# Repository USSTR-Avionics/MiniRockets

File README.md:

# University of Saskatchewan Space Design Team: Avionics

---

# Rocket Autonomy System

Welcome to the Rocket Autonomy System project, developed by the University of Saskatchewan Space Design Team (USST). This software project aims to create a complete autonomous system for rockets.

## Project Overview

The primary goal of this project is to design and implement an autonomous system for rockets that exhibits three main capabilities:

1. **Command**: The system is designed to send/receive commands to/from a ground station in real-time. It should also be capable of executing received commands on the rocket promptly.

2. **Control**: The system will quasi-autonomously control the rocket, ensuring stable flight state detection. This includes phases such as powered flight, ballistic descent, and controlled parachute deployment.

3. **Data Acquisition**: The system must collect data from various sensors within the rocket. Collected data should be transmitted to the ground station in real-time, enabling real-time monitoring and analysis of the rocket's performance during flight.

## Key Objectives

The Rocket Autonomy System project encompasses the following key objectives:

- **Parachute Deployment**: The system will implement logic for accurate deployment of a parachute at the rocket's apogee, ensuring a safe descent and recovery.

- **Data Collection and Storage**: The system will gather sensor data from onboard components, including accelerometers, barometric pressure sensors, thermocouples, and other relevant sensors. Collected data will be stored for analysis.

- **Ground Station Communication**: The system will establish a robust communication link between the rocket and a ground station. This link enables real-time exchange of commands and telemetry data, enhancing situational awareness and control.

## Mini Rocket Flight Computer Prototype

The project began with the development of the Mini Rocket Flight Computer prototype. This early prototype was crafted using commercial off-the-shelf breakout boards assembled onto PCBs. The prototype aimed to demonstrate the system's capabilities, including:

- Parachute deployment
- Data logging from sensors

### PCB Design

The PCB design was completed using Eagle, a commonly used PCB design tool.

### Version 1 (Engineering Model)

The initial version, known as the Engineering Model, served as a proof of concept. It successfully demonstrated the planned functionalities, laying the foundation for the Rocket Autonomy System project.

### Version 2 (Flight Model)

The second version, referred to as the Flight Model, brought significant enhancements to the Mini Rocket Flight Computer:

- Added additional breakout boards, including a thermocouple and a 32kByte FRAM for expanded data storage capacity.
- Improved power trace reliability for enhanced performance and reliability.
- Incorporated design modifications, including a gap in the middle of the system to meet aerostructure requirements.

#### Sensors

A variety of commercial off-the-shelf breakout sensors were utilized to develop and test the design rapidly. The design involved testing the following breakout boards:

- Teensy 4.1 Development Board (PJRC)
- KX134 Breakout (SparkFun)
- BNO055 IMU Breakout (Adafruit)
- BMI088 IMU Breakout (Mouser)
- MS5611 Breakout (Smart Prototyping)
- BMP280 Barometer (Adafruit)
- 32kByte FRAM Breakout (Adafruit)
- MAX31855 Thermocouple Breakout (Adafruit)
- RFM95W LoRa Radio Transceiver Breakout (Adafruit)
- DMC809 Servo Motors (RobotShop) (Not used in the final design)

#### Software

The software was written in C++ using PlatformIO in Visual Studio Code.

#### Lessons Learned

Through the development process, the team gained valuable insights:

- Teensy 4.1 is highly efficient for rapid code development.
- KX134 accelerometer is exceptionally capable, measuring up to 64g's of acceleration.
- BNO055's sensor fusion algorithms aren't suitable for rockets due to their dependency on downward acceleration being 9.81m/s^2.
- BMI088 worked well, but its non-standard header pins posed challenges for breadboard testing.
- MS5611 and BMP280 performed effectively.
- 32kBytes of FRAM storage proved barely sufficient for minimal rocket data, even with data compression.
- MAX31855 reliably operated, even with thermocouples from different suppliers.
- RFM95W LoRa Radios functioned well, though integrating libraries into PlatformIO presented some difficulties.
- Servo motors are unsuitable for parachute deployment systems.
- Modularization was vital, with the main program containing only essential components.

Thank you for your interest in the Rocket Autonomy System project. Together, we can push the boundaries of rocket technology and contribute to the advancement of autonomous rocket systems.

<p align="center">  </img> </p>

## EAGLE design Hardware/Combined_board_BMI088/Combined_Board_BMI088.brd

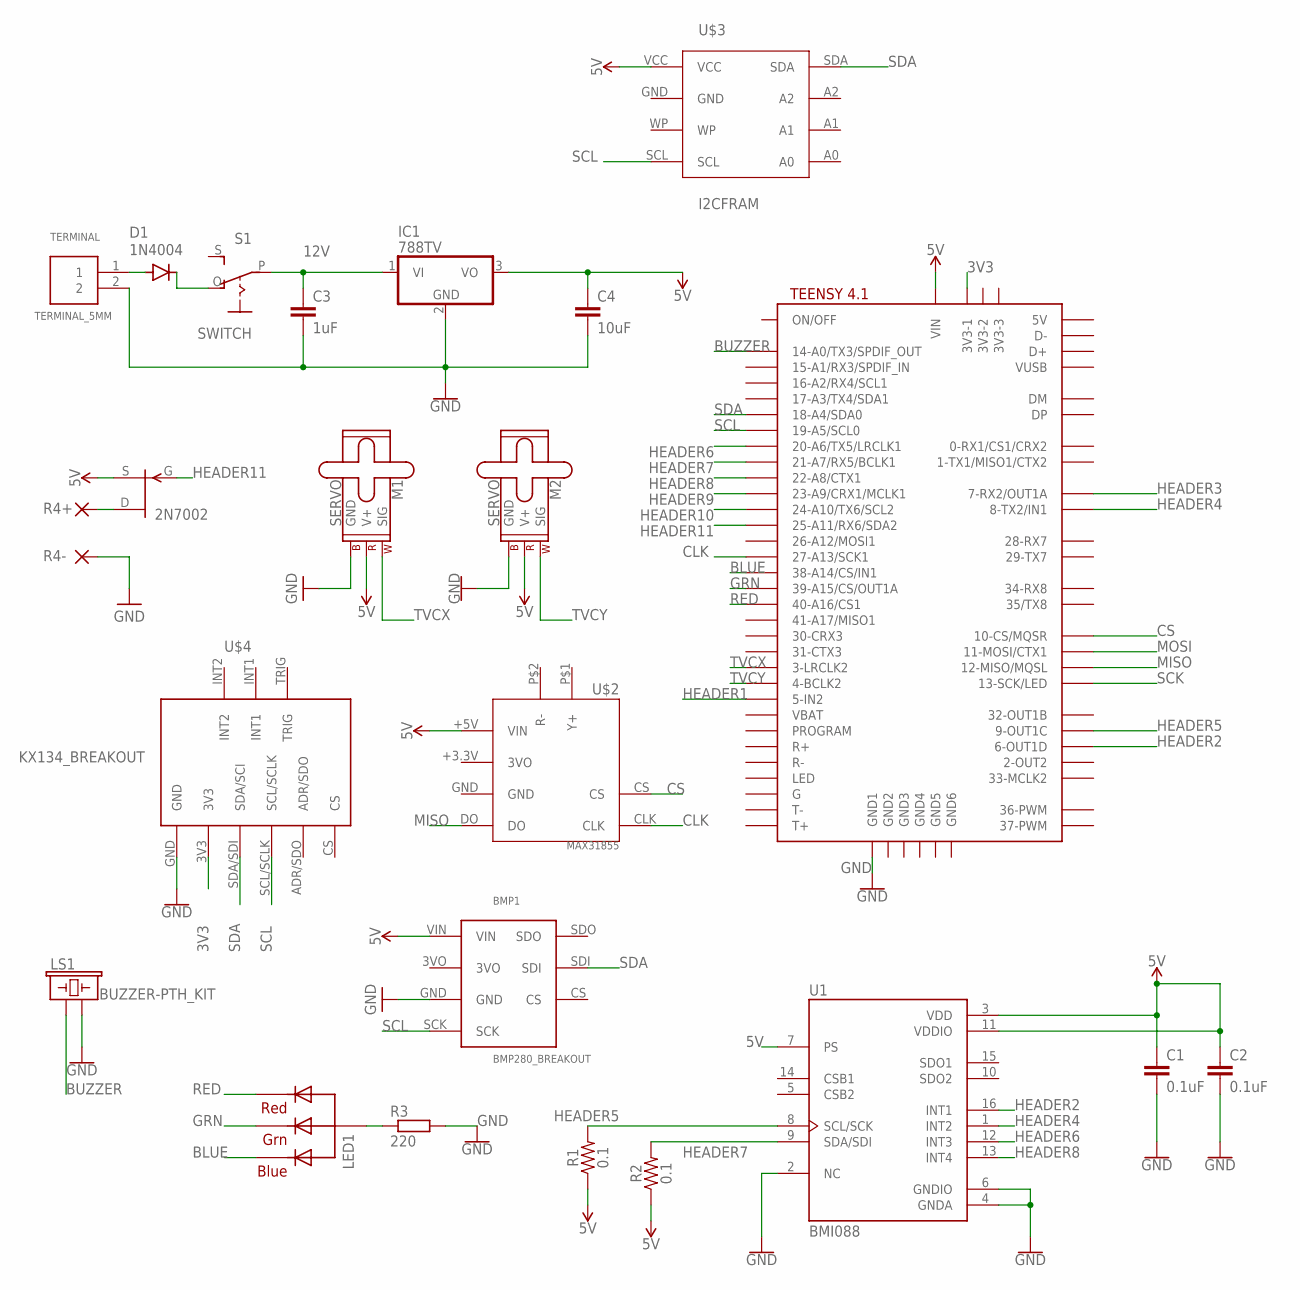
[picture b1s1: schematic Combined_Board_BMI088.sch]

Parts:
2N7002: 2N3819; TO92
BMP1: BMP280_BREAKOUT
C1, C2: 0.1uF; 0402
C3: 1uF; CAP-PTH-2.54
C4: 10uF; CAP-PTH-2.54
D1: 1N4004; DO41-10
IC1: 788TV; TO220V
LED1: RGBLED_CA-5MM; LED5MMRGB
LS1: BUZZER-PTH_KIT; BUZZER-12MM-KIT
M1, M2: SERVO; 1X03
R1, R2: 0.1; 0603
R3: 220; 0204/7
R4+, R4-: 1,6/0,8
S1: SWITCH; EG1218
TERMINAL: TERMINAL_5MM
U1: BMI088; PQFN50P450X300X100-16N
U$1: TEENSY41
U$2: MAX31855; MAX31855-BREAKOUT
U$3: I2CFRAM
U$4: KX134_BREAKOUT

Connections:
3V3: U$1.3V3-1, U$4.3V3
5V: 2N7002.3 (S), BMP1.VIN, C1.1, C2.1, C4.1, IC1.3 (VO), M1.2 (V+), M2.2 (V+), R1.1, R2.1, U1.3 (VDD), U1.7 (PS), U1.11 (VDDIO), U$1.VIN, U$2.+5V (VIN), U$3.VCC
12V: C3.1, IC1.1 (VI), S1.P
BLUE: LED1.4 (BLUE), U$1.38-A14/CS/IN1
BUZZER: LS1.+ (1), U$1.14-A0/TX3/SPDIF_OUT
CLK: U$1.27-A13/SCK1, U$2.CLK
CS: U$1.10-CS\MQSR (10-CS/MQSR), U$2.CS
GND: BMP1.GND, C1.2, C2.2, C3.2, C4.2, IC1.2 (GND), LS1.- (2), M1.3 (GND), M2.3 (GND), R3.2, R4-.1, TERMINAL.2, U1.2 (NC), U1.4 (GNDA), U1.6 (GNDIO), U$1.GND1, U$4.GND
GRN: LED1.3 (GREEN), U$1.39-A15/CS/OUT1A
HEADER1: U$1.5-IN2
HEADER2: U1.16 (INT1), U$1.6-OUT1D
HEADER3: U$1.7-RX2/OUT1A
HEADER4: U1.1 (INT2), U$1.8-TX2/IN2 (8-TX2/IN1)
HEADER5: R1.2, U1.8 (SCL/SCK), U$1.9-OUT1C
HEADER6: U1.12 (INT3), U$1.20-A6/TX5/LRCLK1
HEADER7: R2.2, U1.9 (SDA/SDI), U$1.21-A7/RX5/BCLK1
HEADER8: U1.13 (INT4), U$1.22-A8/CTX1
HEADER9: U$1.23-A9/CRX1/MCLK1
HEADER10: U$1.24-A10/TX6/SCL2
HEADER11: 2N7002.2 (G), U$1.25-A11/RX6/SDA2
MISO: U$1.12-MISO/MQSL, U$2.DO
MOSI: U$1.11-MOSI/CTX1
unnamed: LED1.2 (VCC), R3.1
unnamed: D1.A, TERMINAL.1
unnamed: 2N7002.1 (D), R4+.1
unnamed: D1.C, S1.O
RED: LED1.1 (RED), U$1.40-A16/CS1
SCK: U$1.13-SCK/LED
SCL: BMP1.SCK, U$1.19-A5/SCL0, U$3.SCL, U$4.SCL/SCLK
SDA: BMP1.SDI, U$1.18-A4/SDA0, U$3.SDA, U$4.SDA/SDI (SDA/SCI)
TVCX: M1.1 (SIG), U$1.3-LRCLK2
TVCY: M2.1 (SIG), U$1.4-BCLK2

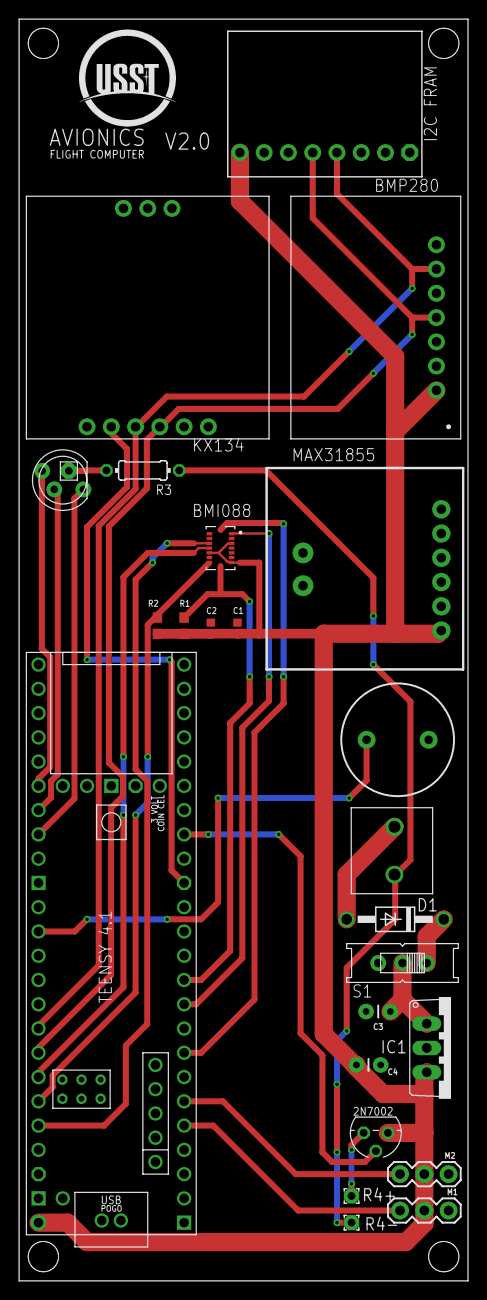
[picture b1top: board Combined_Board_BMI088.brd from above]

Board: 2 copper layers, 47.0 x 132.1 mm, 24 parts (0 on the bottom side), 26 nets.

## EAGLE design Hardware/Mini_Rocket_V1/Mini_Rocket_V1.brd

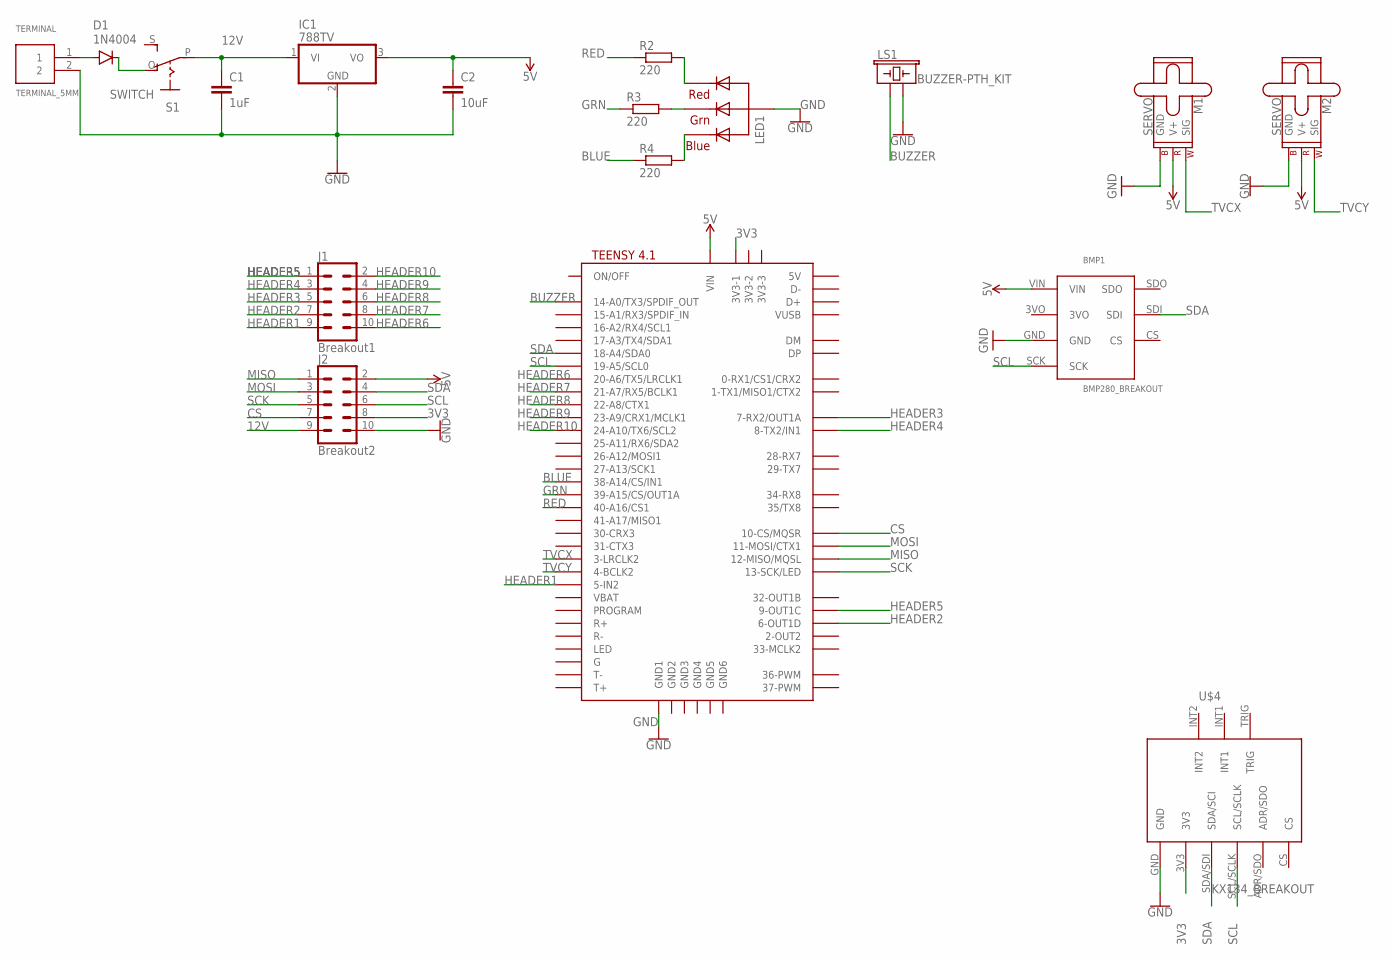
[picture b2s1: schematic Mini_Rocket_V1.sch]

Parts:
BMP1: BMP280_BREAKOUT
C1: 1uF; CAP-PTH-2.54
C2: 10uF; CAP-PTH-2.54
D1: 1N4004; DO41-10
IC1: 788TV; TO220V
J1: Breakout1; 2X5_NOSILK
J2: Breakout2; 2X5_NOSILK
LED1: RGBLED_CA-5MM; LED5MMRGB
LS1: BUZZER-PTH_KIT; BUZZER-12MM-KIT
M1, M2: SERVO; 1X03
R2, R3, R4: 220; 0204/7
S1: SWITCH; EG1218
TERMINAL: TERMINAL_5MM
U$1: TEENSY41
U$4: KX134_BREAKOUT

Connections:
3V3: J2.8, U$1.3V3-1, U$4.3V3
5V: BMP1.VIN, C2.1, IC1.3 (VO), J2.2, M1.2 (V+), M2.2 (V+), U$1.VIN
12V: C1.1, IC1.1 (VI), J2.9, S1.P
BLUE: R4.1, U$1.38-A14/CS/IN1
BUZZER: LS1.+ (1), U$1.14-A0/TX3/SPDIF_OUT
CS: J2.7, U$1.10-CS\MQSR (10-CS/MQSR)
GND: BMP1.GND, C1.2, C2.2, IC1.2 (GND), J2.10, LED1.2 (VCC), LS1.- (2), M1.3 (GND), M2.3 (GND), TERMINAL.2, U$1.GND1, U$4.GND
GRN: R3.1, U$1.39-A15/CS/OUT1A
HEADER1: J1.9, U$1.5-IN2
HEADER2: J1.7, U$1.6-OUT1D
HEADER3: J1.5, U$1.7-RX2/OUT1A
HEADER4: J1.3, U$1.8-TX2/IN2 (8-TX2/IN1)
HEADER5: J1.1, U$1.9-OUT1C
HEADER6: J1.10, U$1.20-A6/TX5/LRCLK1
HEADER7: J1.8, U$1.21-A7/RX5/BCLK1
HEADER8: J1.6, U$1.22-A8/CTX1
HEADER9: J1.4, U$1.23-A9/CRX1/MCLK1
HEADER10: J1.2, U$1.24-A10/TX6/SCL2
MISO: J2.1, U$1.12-MISO/MQSL
MOSI: J2.3, U$1.11-MOSI/CTX1
unnamed: LED1.1 (RED), R2.2
unnamed: LED1.3 (GREEN), R3.2
unnamed: LED1.4 (BLUE), R4.2
unnamed: D1.A, TERMINAL.1
unnamed: D1.C, S1.O
RED: R2.1, U$1.40-A16/CS1
SCK: J2.5, U$1.13-SCK/LED
SCL: BMP1.SCK, J2.6, U$1.19-A5/SCL0, U$4.SCL/SCLK
SDA: BMP1.SDI, J2.4, U$1.18-A4/SDA0, U$4.SDA/SDI (SDA/SCI)
TVCX: M1.1 (SIG), U$1.3-LRCLK2
TVCY: M2.1 (SIG), U$1.4-BCLK2

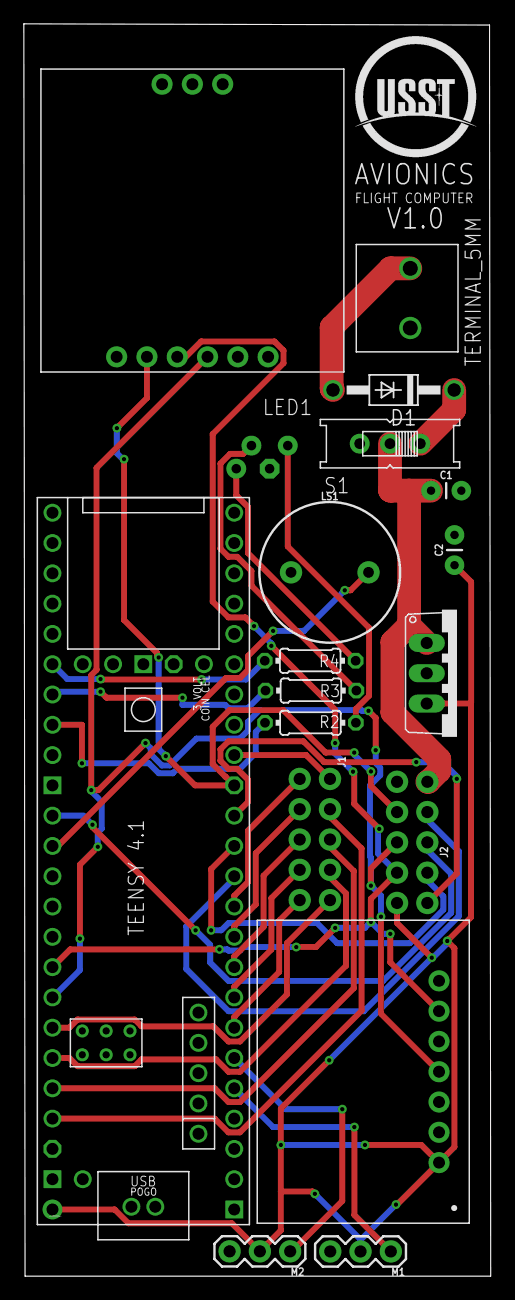
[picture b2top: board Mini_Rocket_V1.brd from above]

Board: 2 copper layers, 39.1 x 105.0 mm, 18 parts (1 on the bottom side), 31 nets.

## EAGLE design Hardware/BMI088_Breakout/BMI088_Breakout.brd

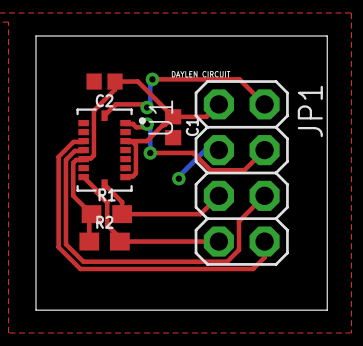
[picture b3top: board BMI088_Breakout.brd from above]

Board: 2 copper layers, 16.2 x 15.2 mm, 6 parts (0 on the bottom side), 8 nets.

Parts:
C1, C2: 0.1uF; 0402
JP1: 2X04
R1, R2: 0.1; 0603
U1: BMI088; PQFN50P450X300X100-16N

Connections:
GND: C1.2, C2.2, JP1.3, U1.2, U1.4, U1.6
HEADER2: JP1.2, U1.16
HEADER4: JP1.4, U1.1
HEADER5: JP1.5, R1.2, U1.8
HEADER6: JP1.6, U1.12
HEADER7: JP1.7, R2.2, U1.9
HEADER8: JP1.8, U1.13
VIN: C1.1, C2.1, JP1.1, R1.1, R2.1, U1.3, U1.7, U1.11

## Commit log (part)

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2022-10-30 completed write()
2022-10-30 removed rounding
2022-10-30 Finished IO functions(write(), read())
2022-10-30 Finished prototyping IO functions(write(), read()), 2's complement might be a concern
2022-10-30 added rounding
2022-10-30 increased memory limit 32k -> 32.768k
2022-10-30 added some comments
2022-10-30 updated .gitignore
2022-10-30 working on float representation in memory
2022-10-31 resolved merge conflicts
2022-10-31 mostly in sync with .ino code except for kalman filters, added preflight software checklist
2022-10-31 deleted inner .gitignore
2022-10-31 updated git cache on local
2022-10-31 started work on interface for fram writers
2022-11-01 patched m_Addr changes
2022-11-02 converting state stuct to enum
2022-11-02 fixed const char*
2022-11-02 deleted struct'
2022-11-02 FLODEF changed to not move into powered flight on rest
2022-11-05 read and write calculation tested and fixed
2022-11-06 0.4.0 - refactored code; tbd impl bmi088
2022-11-06 cleaned up meetTheTeam
2022-11-06 fixed merge conflicts
2022-11-06 added basic api abstraction for bmi088
2022-11-07 added i2c scanner, bmp280 returns no data
2022-11-07 bmp280 uses relative height
2022-11-07 sd does not work because builtin_sd macro not in lib
2022-11-08 added support for external LED
2022-11-08 implemented some util and settings, working on the handshake
2022-11-08 constructor fix
2022-11-09 need to perform hand shake
2022-11-11 0.5.0 - changed delays back to millis
2022-11-11 Added comments to main.cpp
2022-11-11 need testing
2022-11-11 removed unnecessary recursive call
2022-11-11 removed actions
2022-11-12 RX.cpp
2022-11-12 Avionics RX
2022-11-12 push
2022-11-13 added radiohead library
2022-11-19 added eagle files
2022-11-19 sd card module works sometimes
2022-11-19 fails init
2022-11-20 0.6.0 - updated SD lib
2022-11-26 added thermocouple library
2022-12-01 0.7.0 - added bmp280 relative altitude; added param defs in headers
2022-12-02 return a boxed struct; int/float -> string
2022-12-02 0.8.0 - logging to SD card now works
2022-12-02 0.9.0 - refactored and cleaned up code
2022-12-02 0.8.1 - fixed const char * declaration in header
2022-12-02 0.8.3 - fixed csv formatting
2022-12-03 0.8.4 - discriminating event and data log(s)
2022-12-03 sd works again
2022-12-24 Changed how serial data was printed out in flight (only have comma delimited values in the serial output if not in debug)
2022-12-24 Fixed ground idle to powered flight flawed transition state
2022-12-24 Fixed flawed transition from powered to unpowered flight. When acceleration < Liftoff_threshold it should transition to next state, also flawed implementation of millis() time check is fixed
2022-12-25 Updated apogee check function to properly detect apogee
2022-12-25 Updated deployment and land safe code
2022-12-26 modified led pins and added buzzer module
2022-12-28 Cleaned up code, added a test mode which currently allows the program to enter any state for testing purposes, made .h file for user variables that can be edited depending on what the user wants to t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
2022-12-28 added some more updates to testmode and updates to flight profile in test vs real flight
2022-12-31 updated state machine with MS5611 sensor rather than BMP280 since we are out of BMP280's
2023-01-01 Code clean up and change of vars for presentation
2023-01-14 sync
2023-01-15 general cleanup, cleaned ambiguous operator precedences
2023-01-15 removed random datafile
2023-01-15 fixed ODR violations; do not declare globals in header files!
2023-01-16 break i2c scanner into a debug header
2023-01-16 added ifndef guards
2023-01-16 debug mode is now macro dependent
2023-01-16 0.9.0 - renames and re-wraps
2023-01-16 0.9.1 - added compiler warnings to emit compile mode
2023-01-16 added additional checks to prevent accidental production builds
2023-01-16 consolidated README.md
2023-01-17 0.9.2 - added compiler flags to platform.ini file
2023-01-17 added comments for build flags
2023-01-18 changed doubles to floats; added RFC template
2023-01-21 testing out a workflow
2023-01-21 testing a build fail
2023-01-21 update .ini to include toolchain version
2023-01-21 0.8.5 - restructred folder
2023-01-21 added Links folder
2023-01-21 renamed folders
2023-01-21 Added name to meetTheTeam
2023-01-21 radio setup
2023-01-22 trying to unfuck dev
2023-01-22 trying a force push
2023-01-22 remove
2023-01-22 trying merge
2023-01-22 Removed tuple and smart pointers from radio code
2023-01-22 Added caching
2023-01-22 Added radio to main
2023-01-22 removed rust wrapper for fram
2023-01-23 added link to testing, removed rust code
2023-01-23 tested initial framework, added avionics schematic
2023-01-23 added include guards, native testing causes problem with embedded headers
2023-01-23 working on fram wrapping in cpp
2023-01-25 removed desktop test, restructed fram wrapper
2023-01-25 fram structure changes
2023-01-25 added initial code for accl temp fram
2023-01-25 Dev (#44)
    * removed rust wrapper for fram
    * added link to testing, removed rust code
    * tested initial framework, added avionics schematic
    * added include guards, native testing causes problem with embedded headers
    * cannot build on native
    * working on fram wrapping in cpp
2023-01-25 fram changes
2023-01-26 removed test_mode_state()
2023-01-26 added pragma system_header to lib files to suppress warnings
2023-01-26 moved macros to a separate header
2023-01-26 moved git tutorial link
2023-01-26 fixed extra lib warnings
2023-01-28 why is testing such a pain
2023-01-28 code kinda gets stuck
2023-01-28 ignore ds_store
2023-01-28 ds_store
2023-01-28 Full radio code test
2023-01-28 Updated servo code
2023-01-29 minor refactor
2023-01-29 cleaning up...
2023-01-30 working towards clean code
2023-01-30 0.9.3 - using extern with globals in header files
2023-01-30 fixed variable shadowing for globals in func param
2023-01-31 fixed accl bug and more
2023-01-31 merged headers and added a test profile with lower thresholds
2023-01-31 refactor
2023-01-31 impl apogee check for local apogee
2023-01-31 added statistics package
2023-02-01 got watchdog working; boilerplate for thermocouple
2023-02-01 changed the way apogee_check() polls for altitude
2023-02-01 0.9.4 - added a soft recovery state
2023-02-02 added .clang-format file
2023-02-02 ran clang format
2023-02-02 added clang-fmt-linter action
2023-02-02 clang fmt 15
2023-02-02 added lint format action
2023-02-02 automated lint commit
2023-02-02 0.9.5 - added makefile with targets
2023-02-02 changed up workflow
2023-02-02 action rename
2023-02-02 this works pretty well
2023-02-02 0.9.6 - apogee_check() precision and accuracy improved
2023-02-02 added make target: build
2023-02-03 i2c scanner doesn't work, fram not picked up on i2c scan
2023-02-03 0.9.7 - added line enforcements in workflow action
2023-02-03 updated paths in workflow script
2023-02-03 more path updates
2023-02-04 gitignored cmake files and folders
2023-02-04 pre-push hook
2023-02-04 test
2023-02-04 broken
2023-02-04 Version 1 to test
2023-02-04 ver 2 to test
2023-02-04 added my name
2023-02-04 Made write and read temperature work
2023-02-04 Added thermocouple Header and cpp file
2023-02-05 added my name (#50)
2023-02-05 0.9.8 - added make file target for hooks
2023-02-05 target change
2023-02-05 removed telemviewer as a dependency
2023-02-05 added testing template
2023-02-05 eliminated warnings from sensor_sdcard
2023-02-06 credentials change
2023-02-06 deleted dev rule
2023-02-09 file premission changes on local
2023-02-11 another 2 vers to test
2023-02-11 Made write and read temperature work (#54)
2023-02-11 Added thermocouple Header and cpp file without servo code this time
2023-02-11 Added thermocouple Header and cpp file without servo code this time and it compiles
2023-02-11 added mosfet to combine boards
2023-02-12 Added thermocouple code, no servo code (#55)
    * Added servo code and library
    * Updated servo code
    * Added thermocouple Header and cpp file
    * Added thermocouple Header and cpp file without servo code this time
    * Added thermocouple Header and cpp file without servo code this time and it compiles
    ---------
2023-02-12 fixed compilation error in package_fram
2023-02-12 my test
2023-02-14 ver1
2023-02-14 null ptr check
2023-02-18 sync that builds
2023-02-18 i tested around the code, commented out switch mode in RFM95.cpp and it seem to work untill my usb stop letting me upload code :))))
2023-02-19 type on Reset in main
2023-02-23 working on fram data chunk IO
2023-02-23 added the rest of fram impls
2023-02-23 0.10.0 - fram dump doesn't look exactly right
2023-02-23 0.10.1 - made main.cpp line limit compatible
2023-02-23 this should satisfy the linter
2023-02-23 removed erroneous file
2023-02-26 Reduced kill count to 1, Thanks Austin!
2023-02-26 updated apogee check
2023-02-26 0.10.3 - debug_data() only outputs csv compatible with TelemViewer
2023-02-26 more apogee updates, will test new implemention against old one and pick the one that works the best
2023-03-01 Class is now functioning, need to clean up. - radio.init() must be called inside the main file after being manually resetted, any other attempt at working around this has failed (including creating R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
2023-03-02 git ignore system generated
2023-03-02 guard to AVIONICS_RX
2023-03-02 Radio on dev
2023-03-02 fixed RAII resulting in dangling ptr
2023-03-04 Dylan sucks (#59)
    * Combined Avionics board and BMI088 board into on PCB named Combined Board, added space for plunger to fit around the combined board. Changed Avionics board to include a diode and power switch.
    * added mosfet to combine boards
    * Updated flight computer to new version for mini rockets
2023-03-04 0.10.4 - test accel
2023-03-05 should not crash and send messages now
2023-03-05 radio should work properly now
2023-03-05 added write to fram
2023-03-05 added fram checks
2023-03-06 lib changes
2023-03-07 fixed library link
2023-03-07 0.10.4.1 - made apogee check faster-ish
2023-03-07 0.10.5 - manual merge of [PR #60]
2023-03-08 updated compiledb
2023-03-11 forgot const in UDP_Send
2023-03-11 radio integrated tested in the main code base
2023-03-11 Added myself :)
2023-03-11 Added Name and Random Whitespace (#64)
    * Added myself :)
    * sync
    ---------
2023-03-12 work on Flight Activities Program
2023-03-15 working on a fram patch
2023-03-18 fram problem fixed! Switched 8bit -> 16bit
2023-03-18 fram problem fixed! Switched 8bit -> 16bit (#67)
2023-03-19 0.11.0 - documentations galore
2023-03-25 Create LICENSE
2023-03-25 Create LICENSE (#69)
2023-03-29 Organized repository to be more neat
2023-04-01 UDP send no send but crash
2023-04-01 no print current state fram
2023-04-01 wrks nt
2023-04-08 1.0.0 - DO NOT FUCKING TOUCHgit log --oneline!
2023-04-08 did stuff
2023-04-08 datalogger (#71)
    * Combined Avionics board and BMI088 board into on PCB named Combined Board, added space for plunger to fit around the combined board. Changed Avionics board to include a diode and power switch.
    * added mosfet to combine boards
    * Updated flight computer to new version for mini rockets
    * 1.0.0 - DO NOT FUCKING TOUCHgit log --oneline!
    * did stuff
    ---------
2023-04-24 1.1.1 - changes requested by Dylan to set pin to LOW on parachute deploy
2023-04-27 1.1.2 - added a parachute timer to burn the resistor for only 7 seconds
2023-04-27 1.1.3 - added a method to clear FRAM
2023-05-07 1.1.4 - final code
2023-05-09 more last minute changes cause fml
2023-05-10 change
2023-05-10 removed naked return
2023-08-12 Added code of conduct file
2023-08-12 Modified code of conduct file

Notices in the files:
parts and their libraries:
SparkFun-Capacitors: Licensing: Creative Commons ShareAlike 4.0 International - https://creativecommons.org/licenses/by-sa/4.0
